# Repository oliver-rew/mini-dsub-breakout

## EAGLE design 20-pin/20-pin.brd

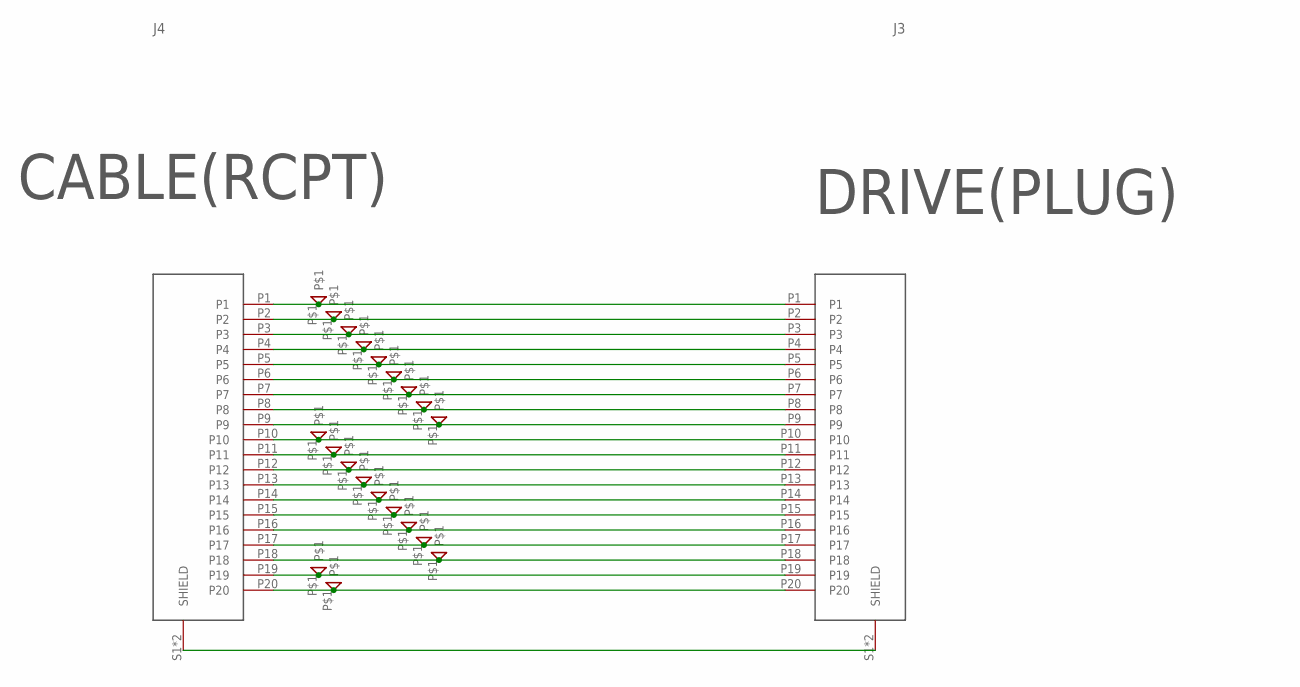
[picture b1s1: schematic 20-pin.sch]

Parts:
J3: 3M_10120-52E2PC(PLUG)
J4: 3M_10220-55H3PC(RECEPTACLE)
U$1, U$2, U$3, U$4, U$5, U$6, U$7, U$8, U$9, U$10, U$11, U$12, U$13, U$14, U$15, U$16, U$17, U$18, U$19, U$20: PTH_SMALL

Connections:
unnamed: J3.P1, J4.P1, U$1.P$1
unnamed: J3.P2, J4.P2, U$2.P$1
unnamed: J3.P3, J4.P3, U$3.P$1
unnamed: J3.P4, J4.P4, U$4.P$1
unnamed: J3.P5, J4.P5, U$5.P$1
unnamed: J3.P6, J4.P6, U$6.P$1
unnamed: J3.P7, J4.P7, U$7.P$1
unnamed: J3.P8, J4.P8, U$8.P$1
unnamed: J3.P9, J4.P9, U$9.P$1
unnamed: J3.P10, J4.P10, U$10.P$1
unnamed: J3.P11, J4.P11, U$11.P$1
unnamed: J3.P12, J4.P12, U$12.P$1
unnamed: J3.P13, J4.P13, U$13.P$1
unnamed: J3.P14, J4.P14, U$14.P$1
unnamed: J3.P15, J4.P15, U$15.P$1
unnamed: J3.P16, J4.P16, U$16.P$1
unnamed: J3.P17, J4.P17, U$17.P$1
unnamed: J3.P18, J4.P18, U$18.P$1
unnamed: J3.P19, J4.P19, U$19.P$1
unnamed: J3.P20, J4.P20, U$20.P$1
SHIELD: J3.S1 (SHIELD), J3.S2 (SHIELD), J4.S1 (SHIELD), J4.S2 (SHIELD)

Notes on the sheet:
DRIVE(PLUG)
CABLE(RCPT)

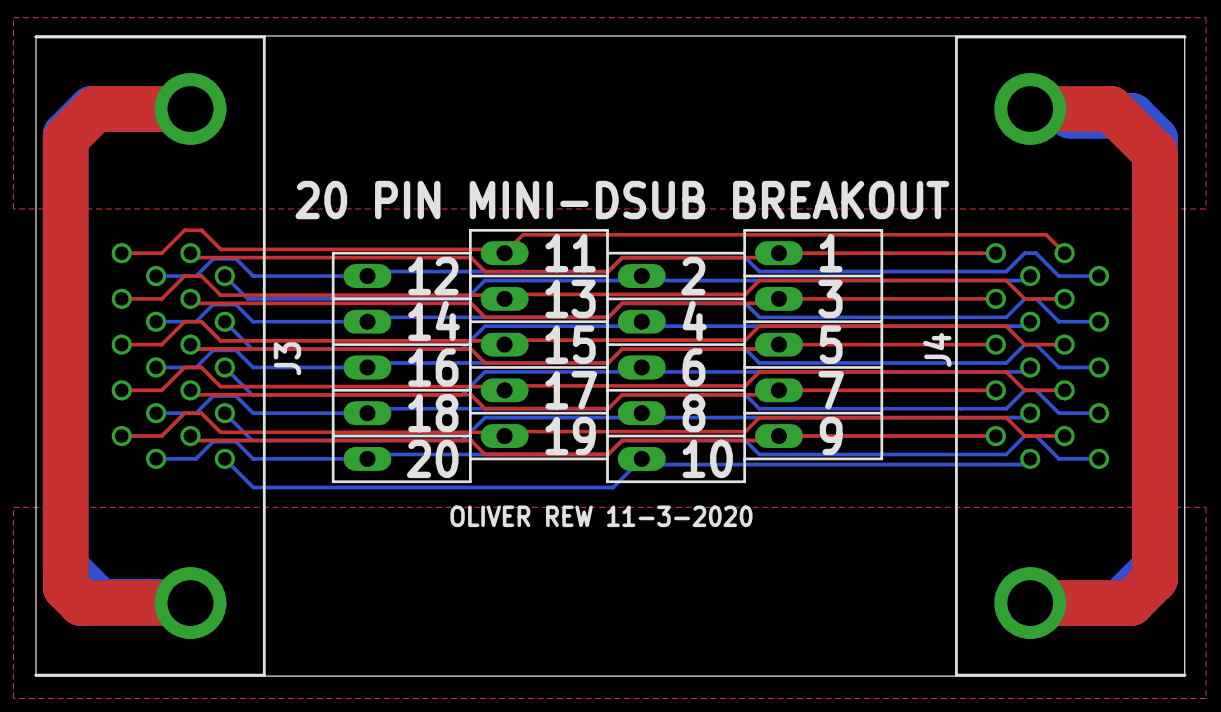
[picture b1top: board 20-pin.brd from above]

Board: 2 copper layers, 63.8 x 35.6 mm, 22 parts (0 on the bottom side), 21 nets.

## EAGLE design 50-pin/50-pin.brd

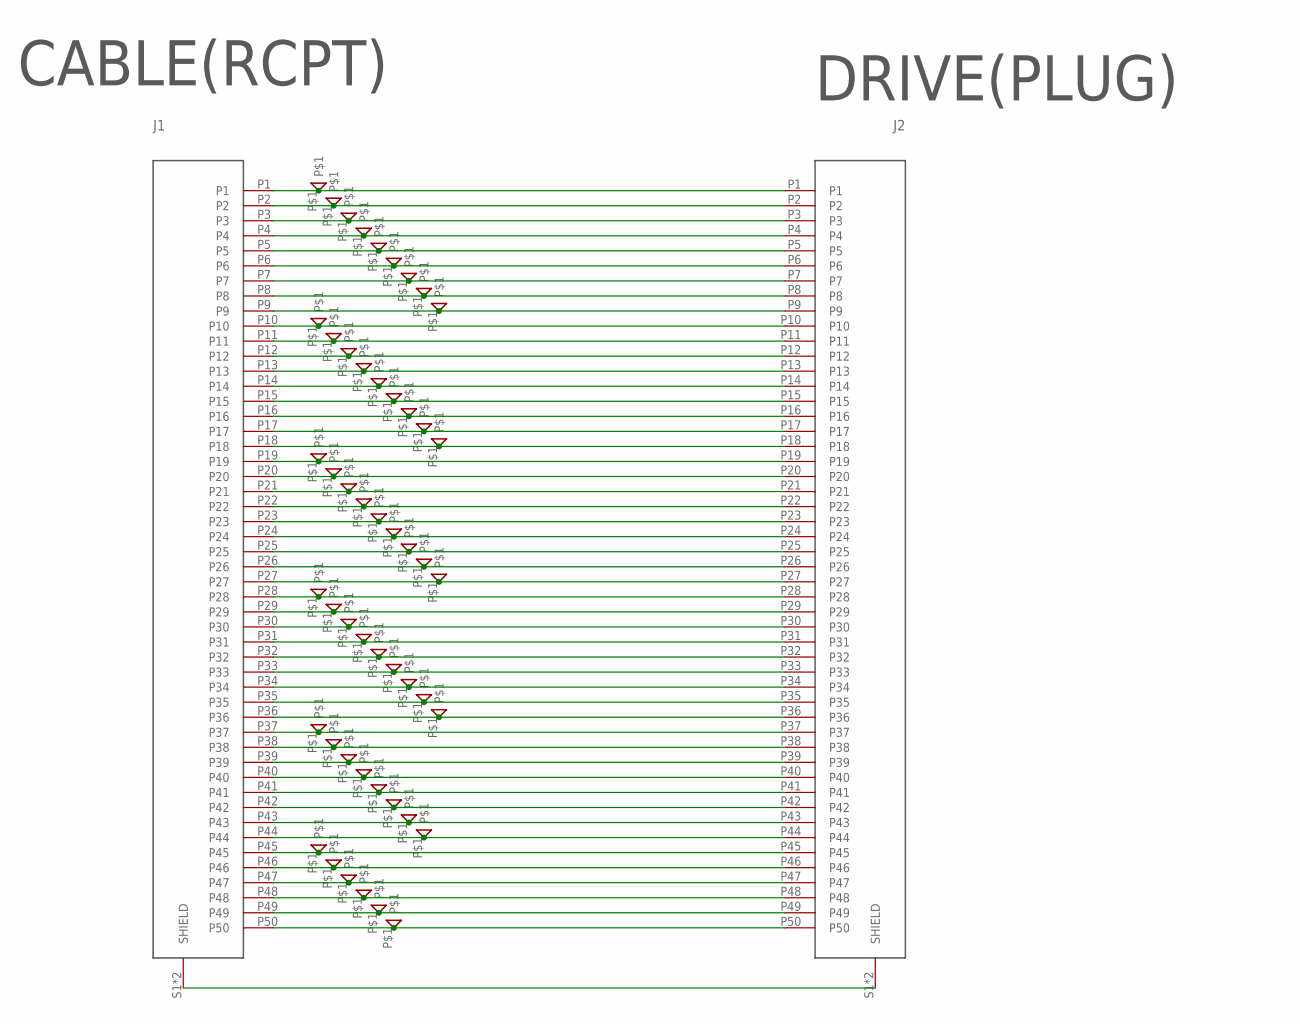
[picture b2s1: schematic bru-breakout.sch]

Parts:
J1: 3M_10250-55H3PC(RECEPTACLE)
J2: 3M_10150-52E2PC(PLUG)
U$1, U$2, U$3, U$4, U$5, U$6, U$7, U$8, U$9, U$10, U$11, U$12, U$13, U$14, U$15, U$16, U$17, U$18, U$19, U$20, U$21, U$22, U$23, U$24, U$25, U$26, U$27, U$28, U$29, U$30, U$31, U$32, U$33, U$34, U$35, U$36, U$37, U$38, U$39, U$40, U$41, U$42, U$43, U$44, U$45, U$46, U$47, U$48, U$49, U$50: PTH_SMALL

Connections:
unnamed: J1.P1, J2.P1, U$1.P$1
unnamed: J1.P2, J2.P2, U$2.P$1
unnamed: J1.P3, J2.P3, U$3.P$1
unnamed: J1.P4, J2.P4, U$4.P$1
unnamed: J1.P5, J2.P5, U$5.P$1
unnamed: J1.P6, J2.P6, U$6.P$1
unnamed: J1.P7, J2.P7, U$7.P$1
unnamed: J1.P8, J2.P8, U$8.P$1
unnamed: J1.P9, J2.P9, U$9.P$1
unnamed: J1.P10, J2.P10, U$10.P$1
unnamed: J1.P11, J2.P11, U$11.P$1
unnamed: J1.P12, J2.P12, U$12.P$1
unnamed: J1.P13, J2.P13, U$13.P$1
unnamed: J1.P14, J2.P14, U$14.P$1
unnamed: J1.P15, J2.P15, U$15.P$1
unnamed: J1.P16, J2.P16, U$16.P$1
unnamed: J1.P17, J2.P17, U$17.P$1
unnamed: J1.P18, J2.P18, U$18.P$1
unnamed: J1.P19, J2.P19, U$19.P$1
unnamed: J1.P20, J2.P20, U$20.P$1
unnamed: J1.P21, J2.P21, U$21.P$1
unnamed: J1.P22, J2.P22, U$22.P$1
unnamed: J1.P23, J2.P23, U$23.P$1
unnamed: J1.P24, J2.P24, U$24.P$1
unnamed: J1.P25, J2.P25, U$25.P$1
unnamed: J1.P26, J2.P26, U$26.P$1
unnamed: J1.P27, J2.P27, U$27.P$1
unnamed: J1.P28, J2.P28, U$28.P$1
unnamed: J1.P29, J2.P29, U$29.P$1
unnamed: J1.P30, J2.P30, U$30.P$1
unnamed: J1.P31, J2.P31, U$31.P$1
unnamed: J1.P32, J2.P32, U$32.P$1
unnamed: J1.P33, J2.P33, U$33.P$1
unnamed: J1.P34, J2.P34, U$34.P$1
unnamed: J1.P35, J2.P35, U$35.P$1
unnamed: J1.P36, J2.P36, U$36.P$1
unnamed: J1.P37, J2.P37, U$37.P$1
unnamed: J1.P38, J2.P38, U$38.P$1
unnamed: J1.P39, J2.P39, U$39.P$1
unnamed: J1.P40, J2.P40, U$40.P$1
unnamed: J1.P41, J2.P41, U$41.P$1
unnamed: J1.P42, J2.P42, U$42.P$1
unnamed: J1.P43, J2.P43, U$43.P$1
unnamed: J1.P44, J2.P44, U$44.P$1
unnamed: J1.P45, J2.P45, U$45.P$1
unnamed: J1.P46, J2.P46, U$46.P$1
unnamed: J1.P47, J2.P47, U$47.P$1
unnamed: J1.P48, J2.P48, U$48.P$1
unnamed: J1.P49, J2.P49, U$49.P$1
unnamed: J1.P50, J2.P50, U$50.P$1
SHIELD: J1.S1 (SHIELD), J1.S2 (SHIELD), J2.S1 (SHIELD), J2.S2 (SHIELD)

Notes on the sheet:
DRIVE(PLUG)
CABLE(RCPT)

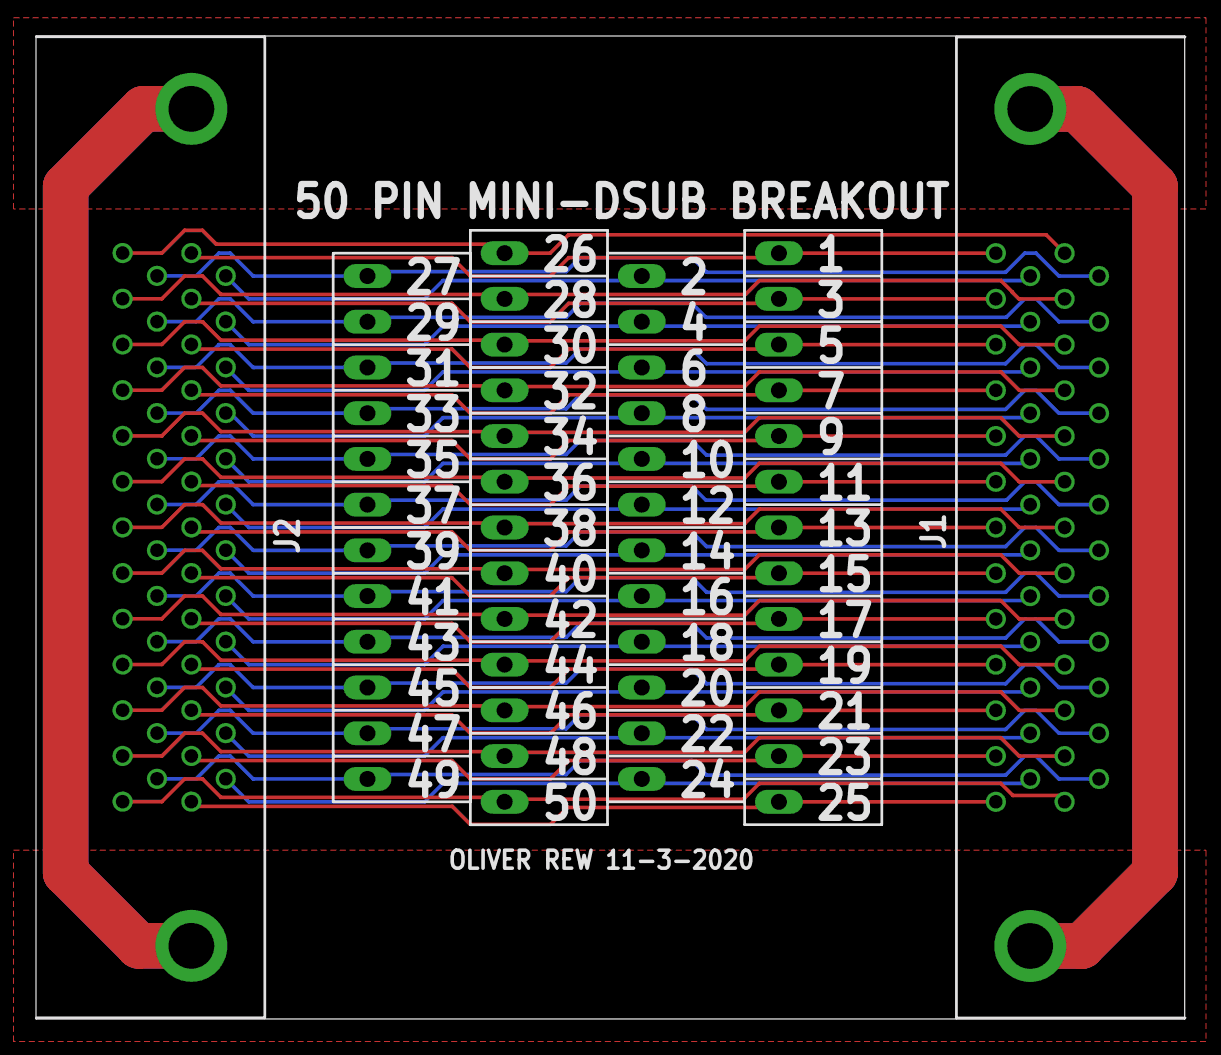
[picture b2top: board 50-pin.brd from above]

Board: 2 copper layers, 63.8 x 54.6 mm, 52 parts (0 on the bottom side), 51 nets.

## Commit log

2020-11-04 added initial 50 pin board
2020-11-04 rename for 50 pin specific board
2020-11-04 added 20 pin
